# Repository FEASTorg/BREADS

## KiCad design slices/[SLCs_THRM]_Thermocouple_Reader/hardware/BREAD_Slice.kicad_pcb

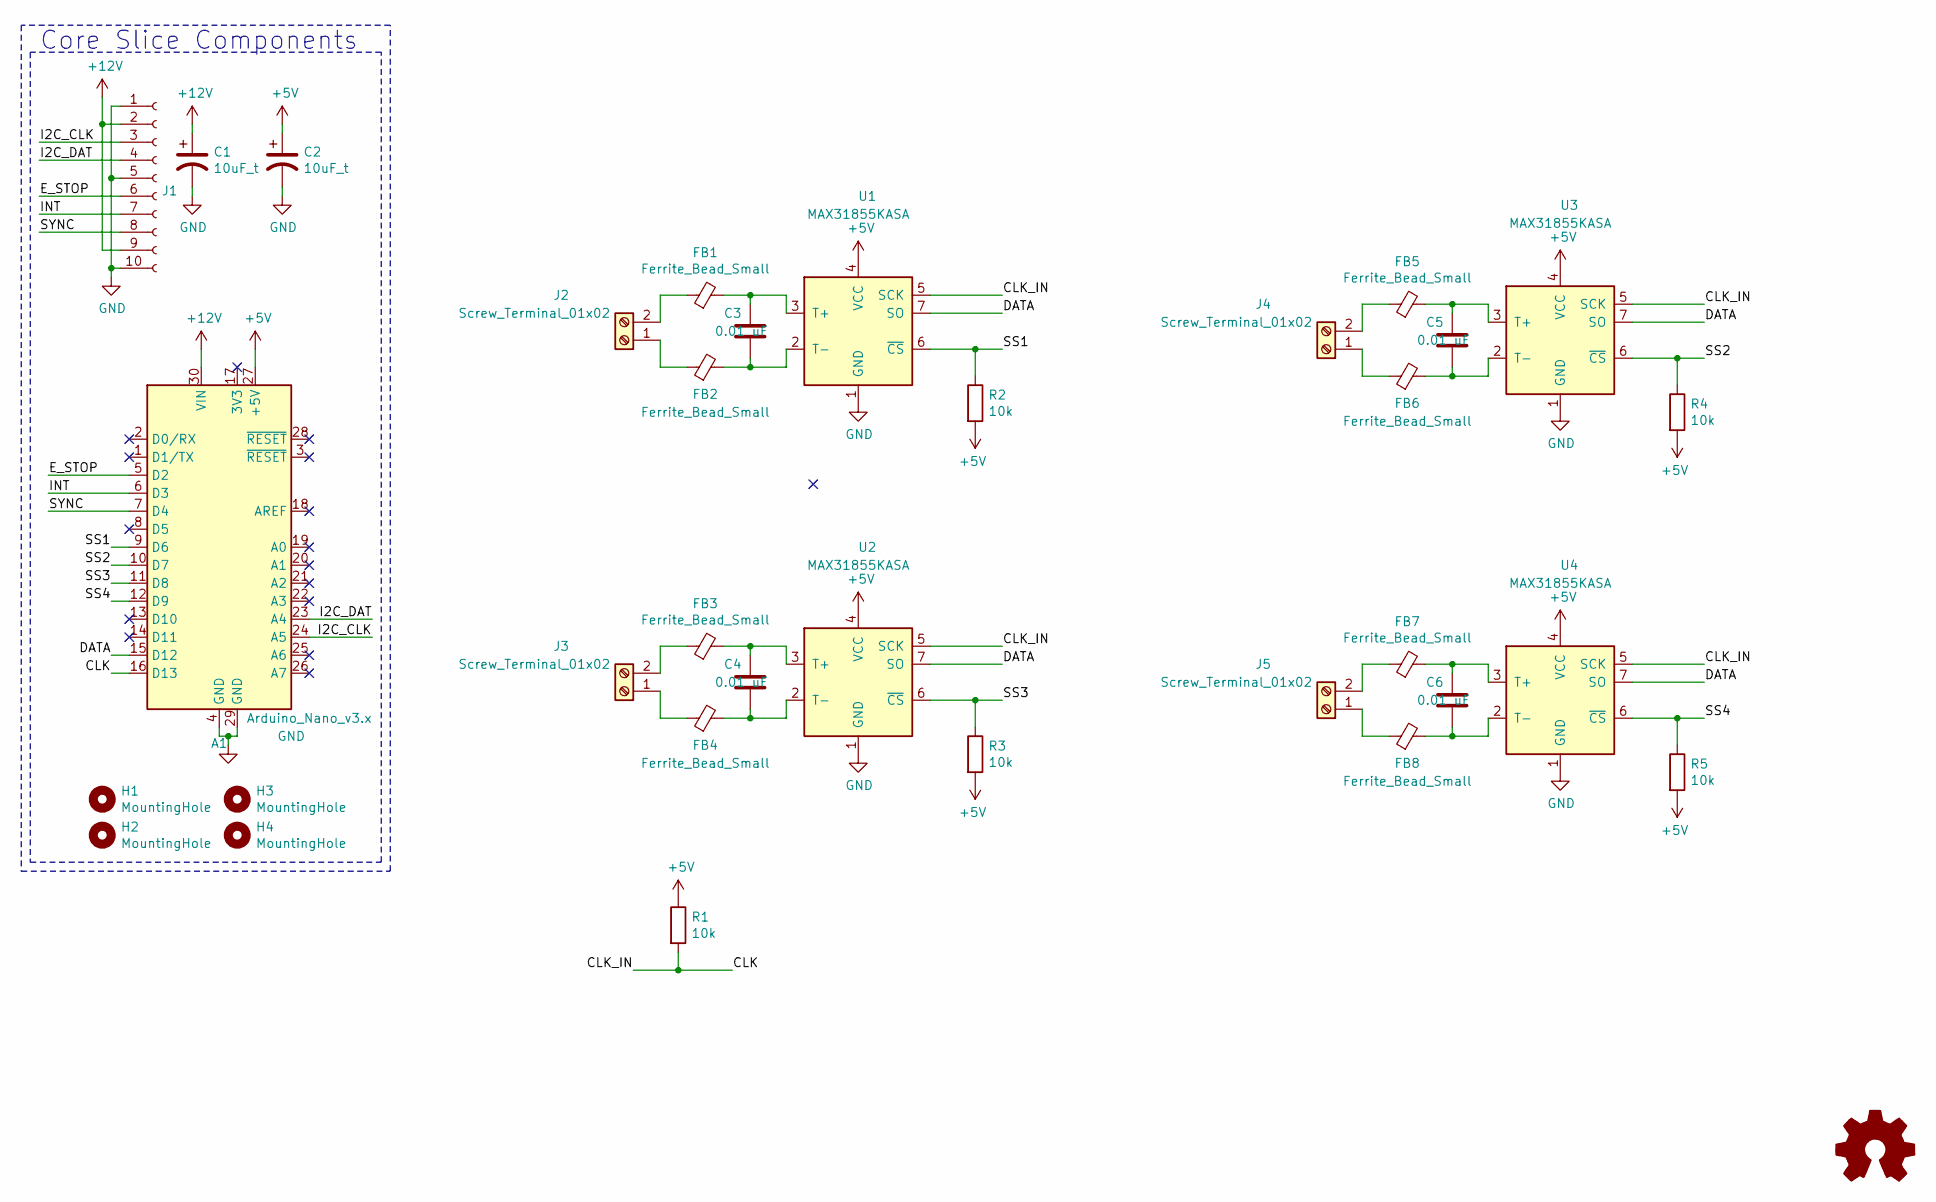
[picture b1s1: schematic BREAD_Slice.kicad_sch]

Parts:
A1: Arduino_Nano_v3.x; Arduino_Nano
C1, C2: 10uF_t; C_2312; Part # T491C106K025AT
C3, C4, C5, C6: 0.01 uF; C_1206_3216Metric_Pad1.33x1.80mm_HandSolder
FB1, FB2, FB3, FB4, FB5, FB6, FB7, FB8: Ferrite_Bead_Small; R_1206_3216Metric_Pad1.30x1.75mm_HandSolder
H1, H2, H3, H4: MountingHole; MountingHole_3.2mm_M3_DIN965_Pad
J1: Conn_01x10_Female; PinSocket_1x10_P2.54mm_Horizontal
J2, J3, J4, J5: Screw_Terminal_01x02; TerminalBlock_TE_282834-2_1x02_P2.54mm_Horizontal
Logo1: Logo_Open_Hardware_Small; OSHW-Symbol_6.7x6mm_SilkScreen
R1, R2, R3, R4, R5: 10k; R_1206_3216Metric_Pad1.30x1.75mm_HandSolder
U1, U2, U3, U4: MAX31855KASA; SOIC-8_3.9x4.9mm_P1.27mm

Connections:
+5V: A1.27 (+5V), C2.1, R1.1, R2.2, R3.2, R4.2, R5.2, U1.4 (VCC), U2.4 (VCC), U3.4 (VCC), U4.4 (VCC)
+12V: A1.30 (VIN), C1.1, J1.2, J1.9
/CLK: A1.16 (D13), R1.2, U1.5 (SCK), U2.5 (SCK), U3.5 (SCK), U4.5 (SCK)
/DATA: A1.15 (D12), U1.7 (SO), U2.7 (SO), U3.7 (SO), U4.7 (SO)
/E_STOP: A1.5 (D2), J1.6
/I2C_CLK: A1.24 (A5), J1.3
/I2C_DAT: A1.23 (A4), J1.4
/INT: A1.6 (D3), J1.7
/SS1: A1.9 (D6), R2.1, U1.6 (~CS)
/SS2: A1.10 (D7), R4.1, U3.6 (~CS)
/SS3: A1.11 (D8), R3.1, U2.6 (~CS)
/SS4: A1.12 (D9), R5.1, U4.6 (~CS)
/SYNC: A1.7 (D4), J1.8
GND: A1.4 (GND), A1.29 (GND), C1.2, C2.2, J1.1, J1.5, J1.10, U1.1 (GND), U2.1 (GND), U3.1 (GND), U4.1 (GND)
unnamed: C3.1, FB1.2, U1.3 (T+)
unnamed: C3.2, FB2.2, U1.2 (T-)
unnamed: C4.1, FB3.2, U2.3 (T+)
unnamed: C4.2, FB4.2, U2.2 (T-)
unnamed: C5.1, FB5.2, U3.3 (T+)
unnamed: C5.2, FB6.2, U3.2 (T-)
unnamed: C6.1, FB7.2, U4.3 (T+)
unnamed: C6.2, FB8.2, U4.2 (T-)
unnamed: FB1.1, J2.2
unnamed: FB2.1, J2.1
unnamed: FB3.1, J3.2
unnamed: FB4.1, J3.1
unnamed: FB5.1, J4.2
unnamed: FB6.1, J4.1
unnamed: FB7.1, J5.2
unnamed: FB8.1, J5.1

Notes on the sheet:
Core Slice Components

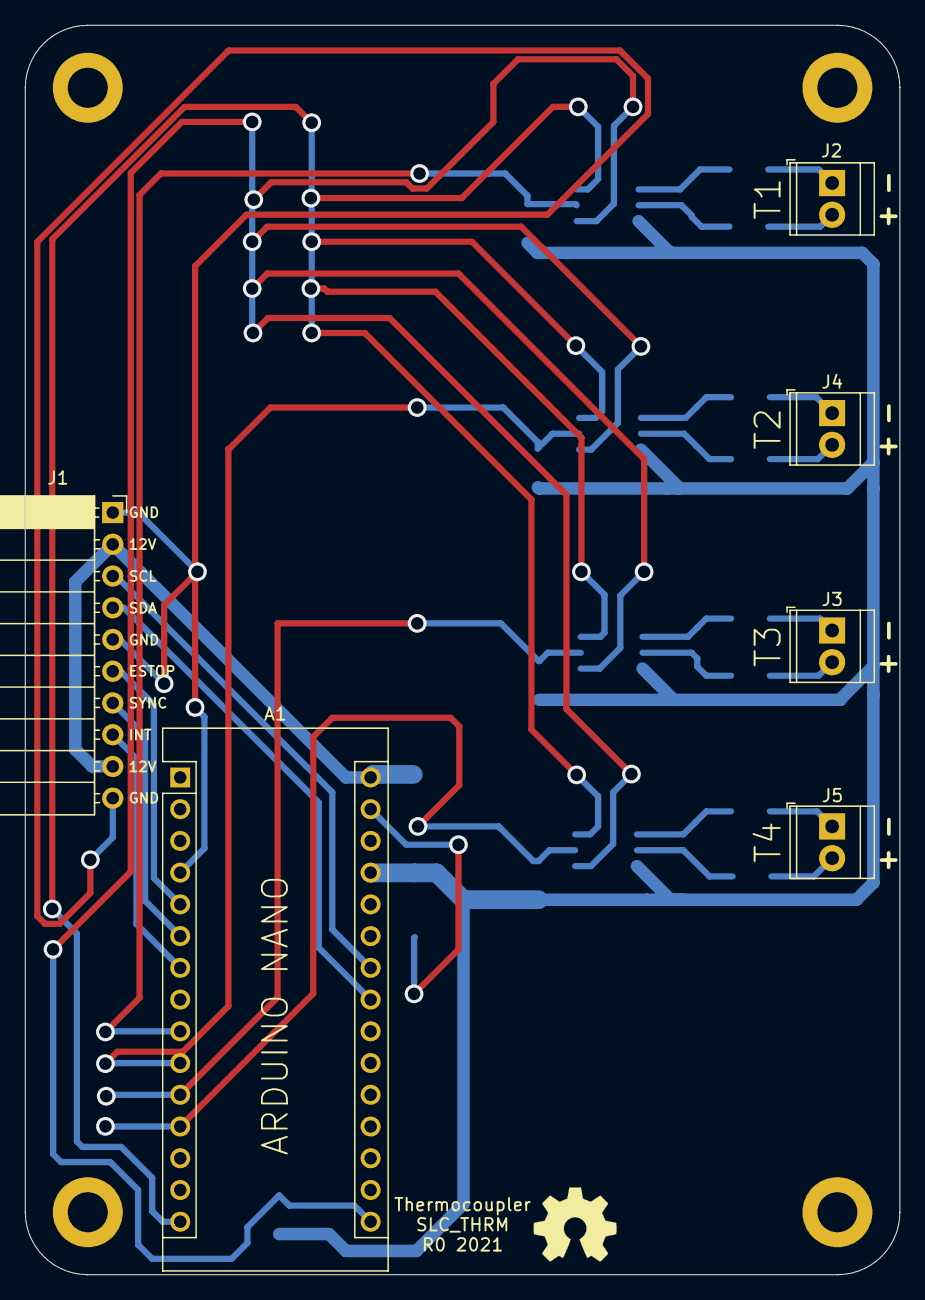
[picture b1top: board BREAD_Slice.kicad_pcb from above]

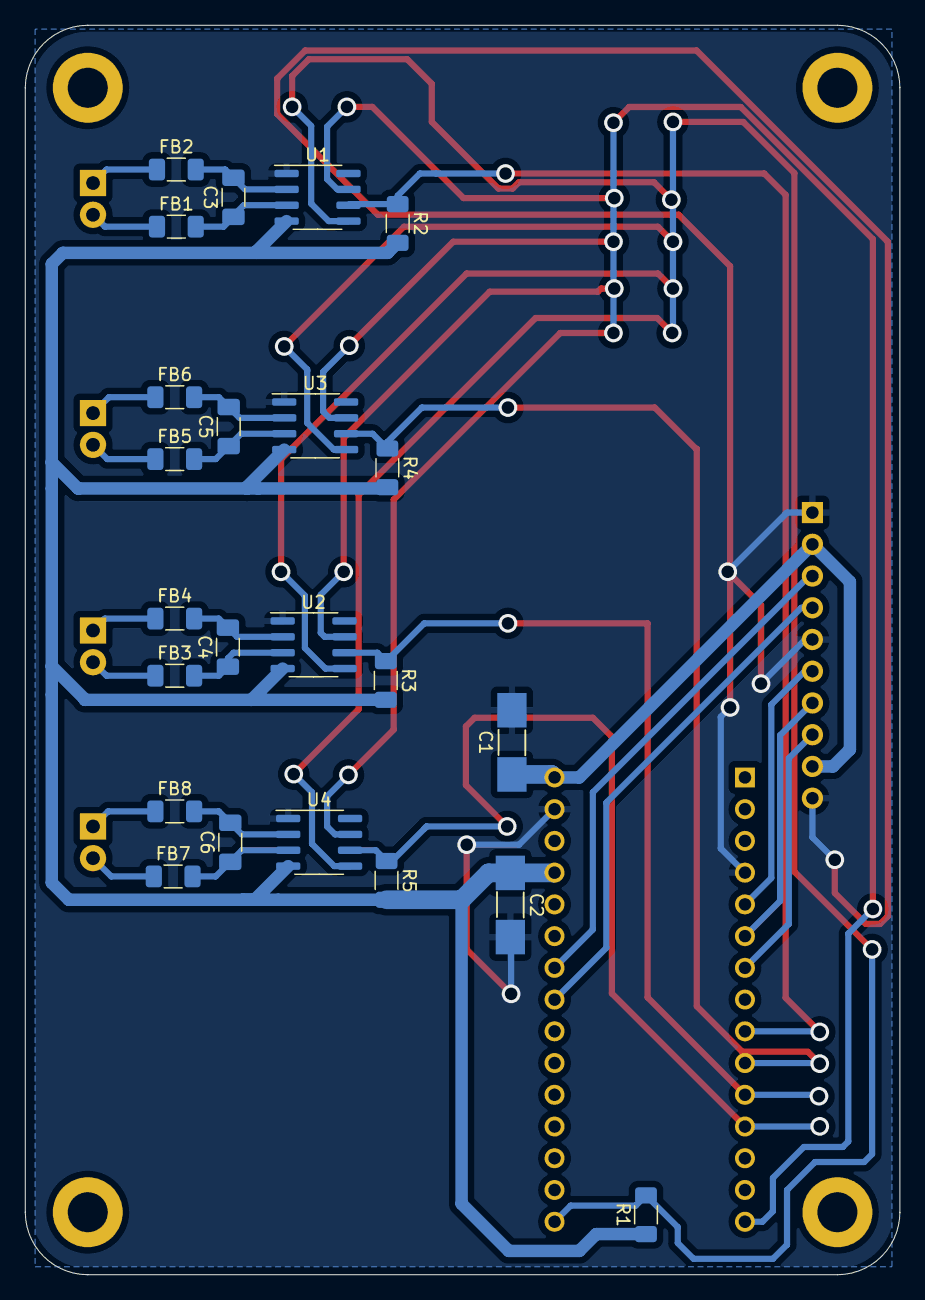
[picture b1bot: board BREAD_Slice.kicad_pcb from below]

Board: 2 copper layers, 70.0 x 100.0 mm, 34 parts (23 on the bottom side), 30 nets.
